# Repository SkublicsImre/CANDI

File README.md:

# CANDI
Control Area Network Diagnostic Instrument (ESP8266-based)

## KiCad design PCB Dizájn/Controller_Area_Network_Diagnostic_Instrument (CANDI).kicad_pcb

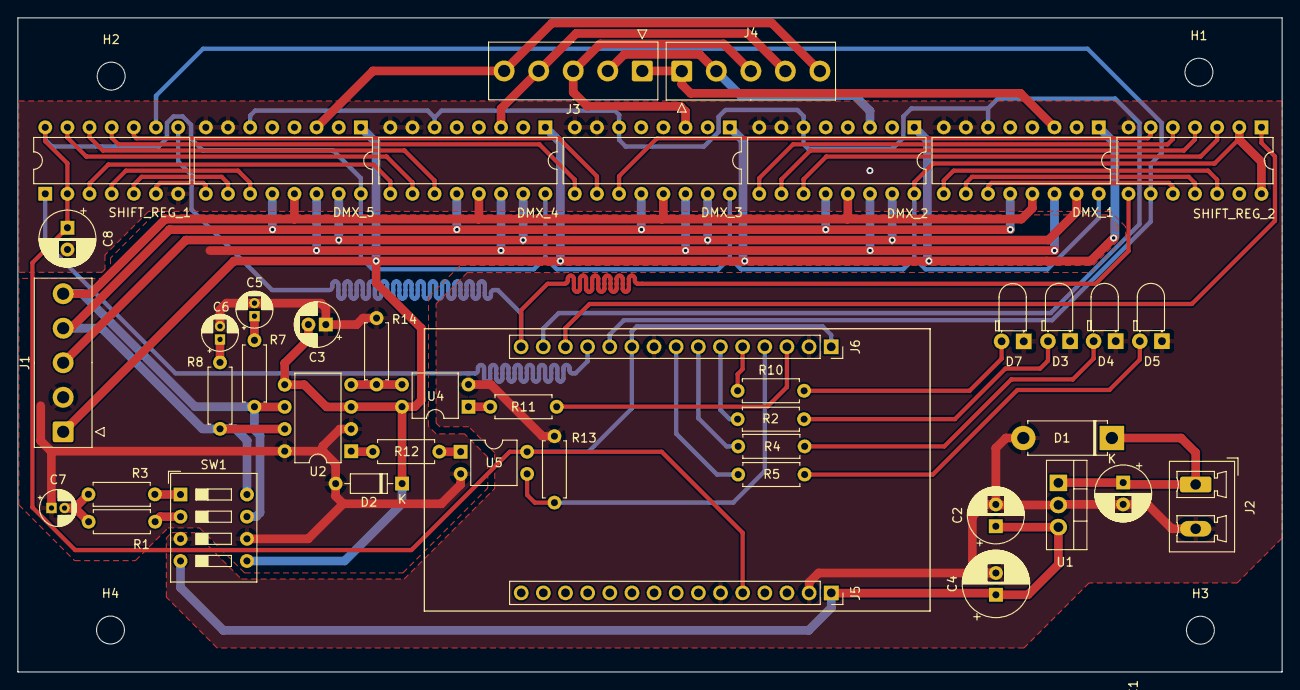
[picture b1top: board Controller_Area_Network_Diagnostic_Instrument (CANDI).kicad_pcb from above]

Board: 2 copper layers, 145.0 x 75.0 mm, 48 parts (0 on the bottom side), 53 nets.

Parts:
C1: 0.22uF; CP_Radial_D6.3mm_P2.50mm
C2, C8: 0.1uF; CP_Radial_D6.3mm_P2.50mm
C3: 0.1uF; CP_Radial_D5.0mm_P2.00mm
C4: 4.7uF; CP_Radial_D7.5mm_P2.50mm
C5, C6, C7: 560pF; CP_Radial_D4.0mm_P1.50mm
D1: SB570; D_5W_P10.16mm_Horizontal
D2: BZX55C6V1; D_DO-35_SOD27_P7.62mm_Horizontal
D3, D4, D5, D7: LED; LED_D3.0mm_Horizontal_O1.27mm_Z2.0mm
DMX_1, DMX_2, DMX_3, DMX_4, DMX_5: 74HC4051; DIP-16_W7.62mm
H1, H2, H3, H4: MountingHole; MountingHole_3.2mm_M3
J1, J3, J4: Screw_Terminal_01x05; TE_826576-5_1x05_P3.96mm_Vertical
J2: Jack-DC (9-12V); PhoenixContact_MCV_1,5_2-G-5.08_1x02_P5.08mm_Vertical
J5, J6: Conn_01x15_Socket; PinSocket_1x15_P2.54mm_Vertical
R1, R3: 60; R_Axial_DIN0207_L6.3mm_D2.5mm_P7.62mm_Horizontal
R2, R4, R5, R10: 500; R_Axial_DIN0207_L6.3mm_D2.5mm_P7.62mm_Horizontal
R7, R8: 100R; R_Axial_DIN0207_L6.3mm_D2.5mm_P7.62mm_Horizontal
R11: 200R; R_Axial_DIN0207_L6.3mm_D2.5mm_P7.62mm_Horizontal
R12: 250R; R_Axial_DIN0207_L6.3mm_D2.5mm_P7.62mm_Horizontal
R13: 1k; R_Axial_DIN0207_L6.3mm_D2.5mm_P7.62mm_Horizontal
R14: 1.2k; R_Axial_DIN0207_L6.3mm_D2.5mm_P7.62mm_Horizontal
SHIFT_REG_1, SHIFT_REG_2: 74HC164; DIP-14_W7.62mm
SW1: SW_DIP_x04; SW_DIP_SPSTx04_Slide_9.78x12.34mm_W7.62mm_P2.54mm
U1: LM7805_TO220; TO-220-3_Vertical
U2: MCP2562-H-P; DIP-8_W7.62mm
U4, U5: SFH617A-1; DIP-4_W7.62mm

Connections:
+3V3: C8.1, DMX_1.16 (VCC), DMX_2.16 (VCC), DMX_3.16 (VCC), DMX_4.16 (VCC), DMX_5.16 (VCC), J5.5, J6.1, J6.10, SHIFT_REG_1.2 (DSB), SHIFT_REG_1.14 (VCC), SHIFT_REG_2.2 (DSB), SHIFT_REG_2.14 (VCC), U5.4
+5VD: C2.1, C4.1, J5.1, SW1.4, U1.3 (VO)
+9V: C1.1, D1.1 (K), J2.1, U1.1 (VI)
CAN_GND: C3.1, C5.2, C6.2, C7.1, D2.2 (A), DMX_1.14 (A1), DMX_2.14 (A1), DMX_3.14 (A1), DMX_4.14 (A1), DMX_5.14 (A1), J1.2, R14.2, SW1.6, U2.2 (VSS), U2.8 (STBY), U5.2
CAN_HI: DMX_1.12 (A3), DMX_2.12 (A3), DMX_3.12 (A3), DMX_4.12 (A3), DMX_5.12 (A3), J1.4, R8.2, SW1.8, U2.7 (CANH)
CAN_LO: DMX_1.13 (A0), DMX_2.13 (A0), DMX_3.13 (A0), DMX_4.13 (A0), DMX_5.13 (A0), J1.5, R7.2, SW1.7, U2.6 (CANL)
CAN_SHLD: DMX_1.15 (A2), DMX_2.15 (A2), DMX_3.15 (A2), DMX_4.15 (A2), DMX_5.15 (A2), J1.3
CAN_V+: C3.2, D2.1 (K), DMX_1.1 (A4), DMX_2.1 (A4), DMX_3.1 (A4), DMX_4.1 (A4), DMX_5.1 (A4), J1.1, SW1.5, U2.3 (VDD), U2.5 (Vio), U4.4
DS1: J6.12, SHIFT_REG_1.1 (DSA)
DS2: J6.13, SHIFT_REG_2.1 (DSA)
En: DMX_1.6 (~E), DMX_2.6 (~E), DMX_3.6 (~E), DMX_4.6 (~E), DMX_5.6 (~E), J6.14
GND: C1.2, C2.2, C4.2, C8.2, D1.2 (A), D3.1 (K), D4.1 (K), D5.1 (K), D7.1 (K), DMX_1.7 (VEE), DMX_1.8 (GND), DMX_2.7 (VEE), DMX_2.8 (GND), DMX_3.7 (VEE), DMX_3.8 (GND), DMX_4.7 (VEE), DMX_4.8 (GND), DMX_5.7 (VEE), DMX_5.8 (GND), J2.2, J5.2, J5.6, J6.2, J6.9, R13.1, SHIFT_REG_1.7 (GND), SHIFT_REG_2.7 (GND), SW1.3, U1.2 (GND), U4.2
In_1: DMX_1.3 (A), J3.1, J4.1
In_2: DMX_2.3 (A), J3.2, J4.2
In_3: DMX_3.3 (A), J3.3, J4.3
In_4: DMX_4.3 (A), J3.4, J4.4
In_5: DMX_5.3 (A), J3.5, J4.5
MR: J6.11, SHIFT_REG_1.9 (~MR), SHIFT_REG_2.9 (~MR)
unnamed: C5.1, R7.1
unnamed: C6.1, R8.1
unnamed: C7.2, R1.2, R3.2
unnamed: D3.2 (A), R2.2
unnamed: D4.2 (A), R4.2
unnamed: D5.2 (A), R5.2
unnamed: D7.2 (A), R10.2
unnamed: DMX_1.11 (S0), SHIFT_REG_2.10 (Q4)
unnamed: DMX_1.10 (S1), SHIFT_REG_2.11 (Q5)
unnamed: DMX_1.9 (S2), SHIFT_REG_2.12 (Q6)
unnamed: DMX_2.11 (S0), SHIFT_REG_2.3 (Q0)
unnamed: DMX_2.10 (S1), SHIFT_REG_2.4 (Q1)
unnamed: DMX_2.9 (S2), SHIFT_REG_2.5 (Q2)
unnamed: DMX_3.11 (S0), SHIFT_REG_2.6 (Q3)
unnamed: DMX_3.10 (S1), SHIFT_REG_1.10 (Q4)
unnamed: DMX_3.9 (S2), SHIFT_REG_1.11 (Q5)
unnamed: DMX_4.11 (S0), SHIFT_REG_1.12 (Q6)
unnamed: DMX_4.10 (S1), SHIFT_REG_1.13 (Q7)
unnamed: DMX_4.9 (S2), SHIFT_REG_1.3 (Q0)
unnamed: DMX_5.11 (S0), SHIFT_REG_1.4 (Q1)
unnamed: DMX_5.10 (S1), SHIFT_REG_1.5 (Q2)
unnamed: DMX_5.9 (S2), SHIFT_REG_1.6 (Q3)
unnamed: J6.5, R10.1
unnamed: J6.6, R2.1
unnamed: J6.7, R4.1
unnamed: J6.8, R5.1
unnamed: R1.1, SW1.2
unnamed: R3.1, SW1.1
unnamed: R11.2, U4.1
unnamed: R12.1, U5.1
unnamed: R14.1, U2.4 (RXD), U4.3
unnamed: R12.2, U2.1 (TXD)
RX: J6.4, R13.2, U5.3
SCLK: J6.15, SHIFT_REG_1.8 (CP), SHIFT_REG_2.8 (CP)
TX: J6.3, R11.1

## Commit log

2025-03-25 Add files via upload
    bunch
2025-03-25 Update CANDI_OS.ino
    missing some debugging functinos
